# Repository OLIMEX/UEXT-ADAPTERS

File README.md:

# UEXT-ADAPTERS
Different UEXT adapters and their CAD files

Proudct pages:

[UEXT-PQ](https://www.olimex.com/Products/Modules/Adapters/UEXT-PQ/open-source-hardware), [UEXT-MPQ](https://www.olimex.com/Products/Modules/Adapters/UEXT-MPQ/open-source-hardware), [UEXT-P4Q](https://www.olimex.com/Products/Modules/Adapters/UEXT-P4Q/open-source-hardware), [RPI-UEXT-MPQ](https://www.olimex.com/Products/Modules/Adapters/RPI-UEXT-MPQ/open-source-hardware).

###Cables:

- regular size UEXT (0.1" ~ 2.54mm pitch):

https://www.olimex.com/Products/Modules/Adapters/CABLE-IDC10-15cm/

- mUEXT (0.05" ~ 1.27mm pitch): 

https://www.olimex.com/Products/Modules/Adapters/mUEXT-CABLE-10-10-1.27/

- pUEXT (1mm pitch):

https://www.olimex.com/Products/Modules/Adapters/pUEXT-CABLE-10-10-50MM/

- Qwiic (Qwiic Stemma compatible 1.0 mm):

https://www.olimex.com/Products/Modules/Adapters/QW-ST-CABLE-4-4-50MM/

###UEXT splitter:

- UEXTx5 (0.1" ~ 2.54mm step):

https://www.olimex.com/Products/Modules/Adapters/UEXTx5/open-source-hardware

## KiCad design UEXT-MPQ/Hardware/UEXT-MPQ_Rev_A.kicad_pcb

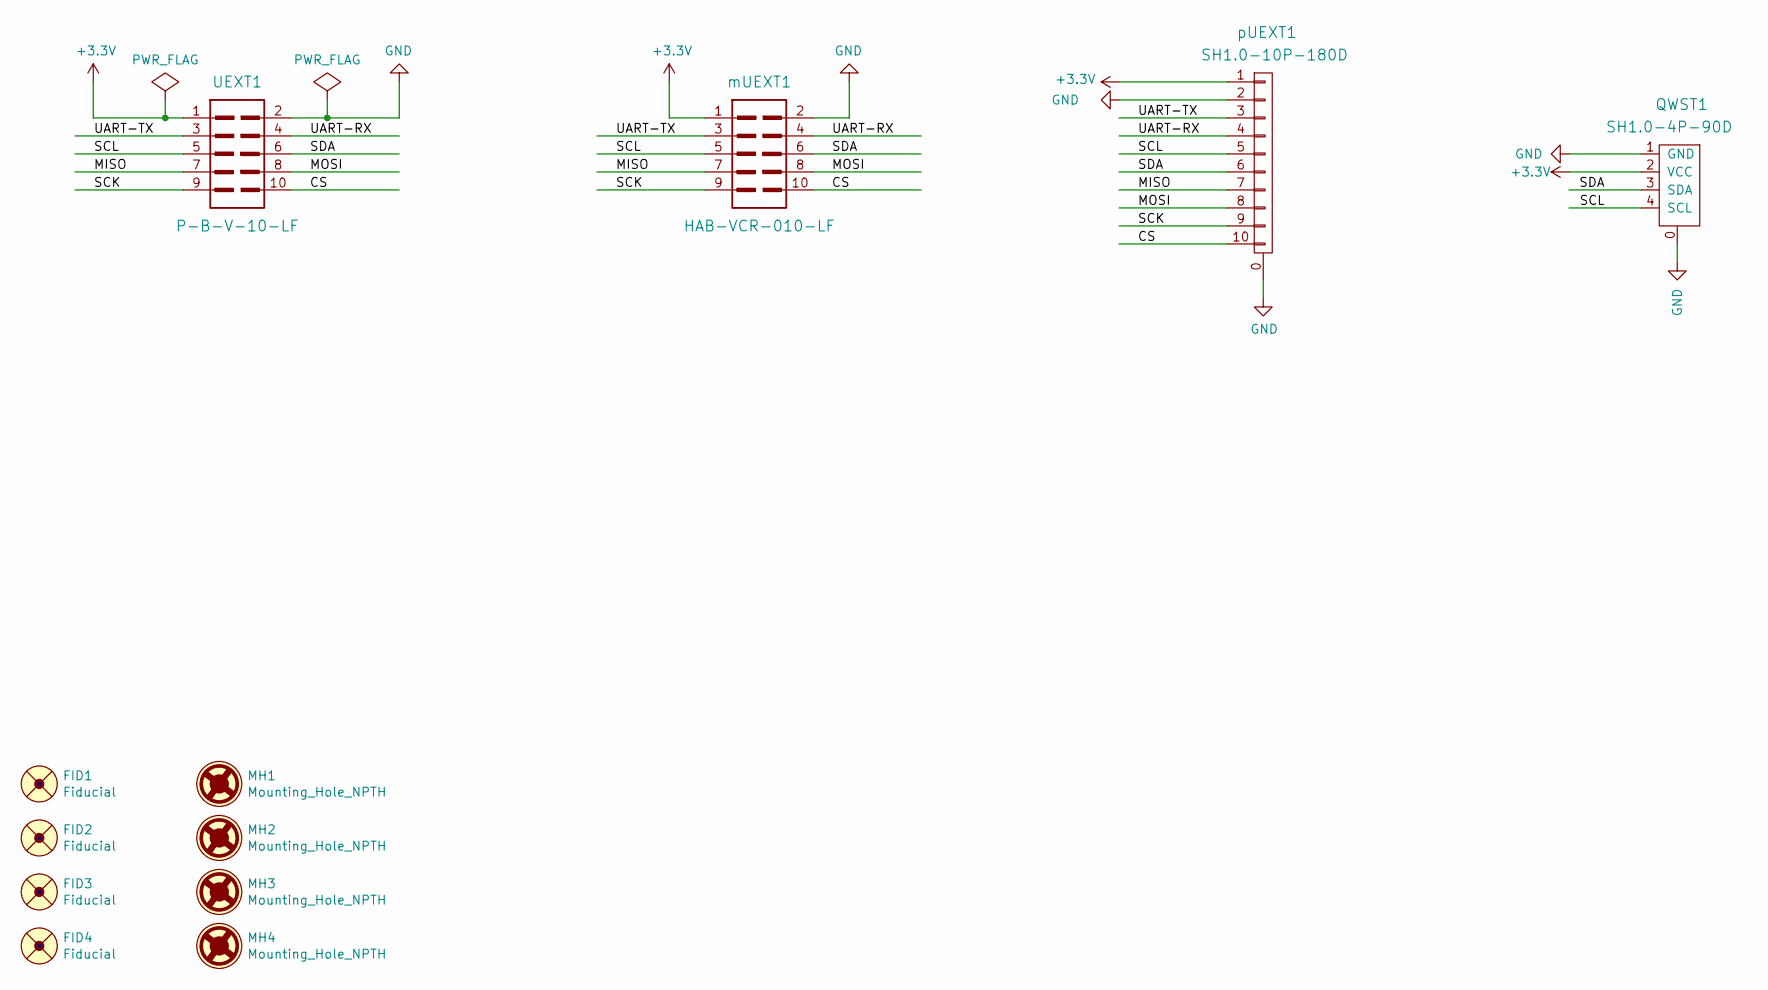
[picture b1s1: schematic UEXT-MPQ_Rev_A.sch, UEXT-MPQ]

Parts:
FID1, FID2, FID3, FID4: Fiducial; Fiducial1x3
MH1, MH2, MH3, MH4: Mounting_Hole_NPTH; Mounting_hole_3.3mm
QWST1: SH1.0-4P-90D; SM04B-SRSS-TB
UEXT1: P-B-V-10-LF; GBH-254-SMT-10
mUEXT1: HAB-VCR-010-LF
pUEXT1: SH1.0-10P-180D; BM10B-SRSS-TB

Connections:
+3.3V: QWST1.2 (VCC), UEXT1.1, mUEXT1.1, pUEXT1.1
/CS: UEXT1.10, mUEXT1.10, pUEXT1.10
/MISO: UEXT1.7, mUEXT1.7, pUEXT1.7
/MOSI: UEXT1.8, mUEXT1.8, pUEXT1.8
/SCK: UEXT1.9, mUEXT1.9, pUEXT1.9
/SCL: QWST1.4 (SCL), UEXT1.5, mUEXT1.5, pUEXT1.5
/SDA: QWST1.3 (SDA), UEXT1.6, mUEXT1.6, pUEXT1.6
/UART-RX: UEXT1.4, mUEXT1.4, pUEXT1.4
/UART-TX: UEXT1.3, mUEXT1.3, pUEXT1.3
GND: QWST1.0, QWST1.1 (GND), UEXT1.2, mUEXT1.2, pUEXT1.0, pUEXT1.2

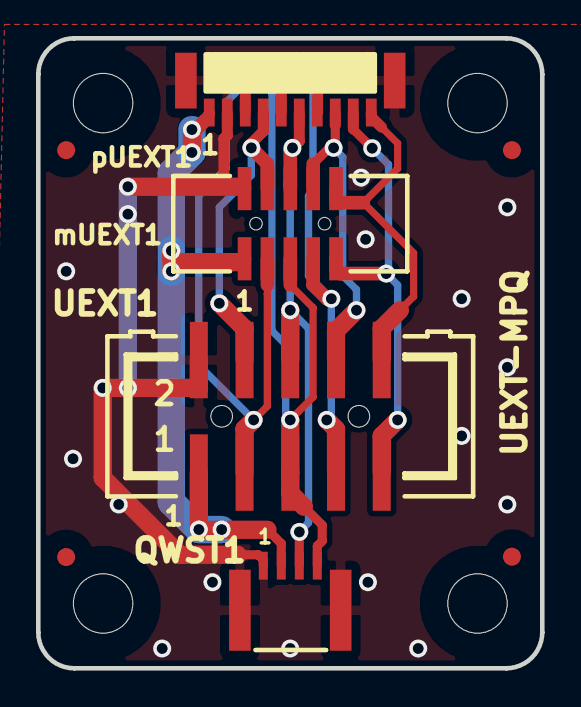
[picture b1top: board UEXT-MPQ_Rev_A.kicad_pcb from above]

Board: 2 copper layers, 28.0 x 35.0 mm, 17 parts (5 on the bottom side), 10 nets.

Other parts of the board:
Antistatic: Val**; LOGO_ANTISTATIC_1
Pb_free: LOGO_PBFREE
Recycle_bin: LOGO_RECYCLEBIN_1
Sign_CE: CE_Sign
Sign_RoHS_1: Sign_RoHS_1

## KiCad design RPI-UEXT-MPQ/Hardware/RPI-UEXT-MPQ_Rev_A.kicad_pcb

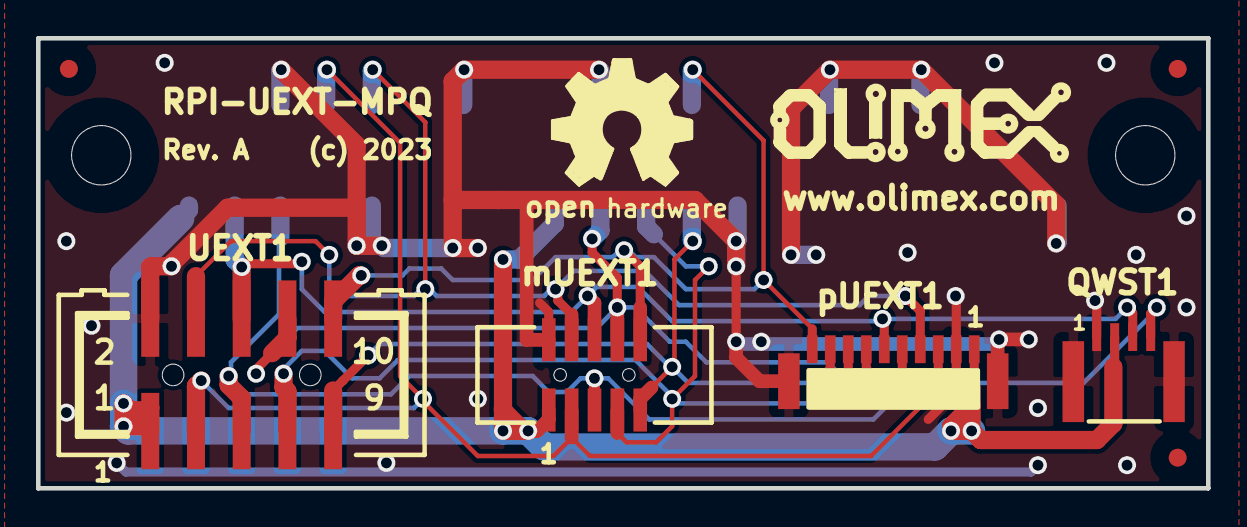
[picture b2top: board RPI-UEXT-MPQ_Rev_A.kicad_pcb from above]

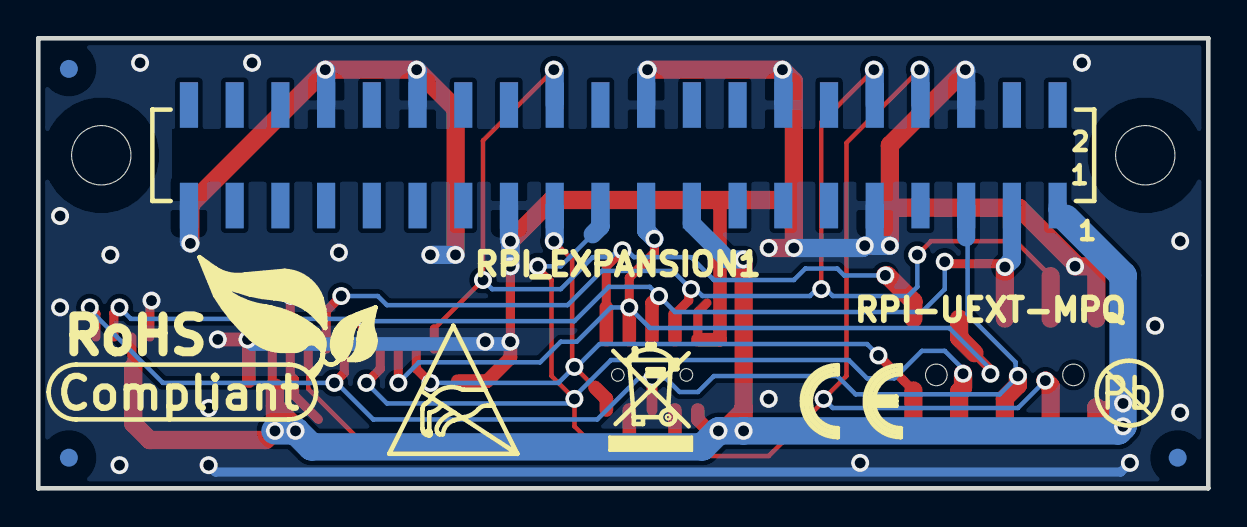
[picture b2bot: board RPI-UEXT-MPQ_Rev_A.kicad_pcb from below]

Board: 2 copper layers, 65.0 x 25.0 mm, 20 parts (9 on the bottom side), 10 nets.

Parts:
FID1, FID2, FID3, FID4, FID5, FID6: Fiducial; Fiducial1x3
Logo_OLIMEX_TB: Logo_OLIMEX_TB
MH1, MH2: Mounting_Hole_NPTH; Mounting_hole_3.3mm
QWST1: SH1.0-4P-90D; SM04B-SRSS-TB
RPI_EXPANSION1: F-V50X-2X20-LF
Sign_Antistatic: Sign_Antistatic
Sign_CE: CE_Sign
Sign_OSHW_8x8: Sign_OSHW_8x8
Sign_PB-Free: Sign_PB-Free
Sign_RecycleBin_1: Sign_RecycleBin_1
Sign_RoHS_1: Sign_RoHS_1
UEXT1: P-B-V-10-LF; GBH-254-SMT-10
mUEXT1: HAB-VCR-010-LF
pUEXT1: SH1.0-10P-180D; BM10B-SRSS-TB

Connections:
+3.3V: QWST1.2, RPI_EXPANSION1.1, RPI_EXPANSION1.17, UEXT1.1, mUEXT1.1, pUEXT1.1
/CS: RPI_EXPANSION1.24, UEXT1.10, mUEXT1.10, pUEXT1.10
/MISO: RPI_EXPANSION1.21, UEXT1.7, mUEXT1.7, pUEXT1.7
/MOSI: RPI_EXPANSION1.19, UEXT1.8, mUEXT1.8, pUEXT1.8
/SCK: RPI_EXPANSION1.23, UEXT1.9, mUEXT1.9, pUEXT1.9
/SCL: QWST1.4, RPI_EXPANSION1.5, UEXT1.5, mUEXT1.5, pUEXT1.5
/SDA: QWST1.3, RPI_EXPANSION1.3, UEXT1.6, mUEXT1.6, pUEXT1.6
/UART-RX: RPI_EXPANSION1.10, UEXT1.4, mUEXT1.4, pUEXT1.4
/UART-TX: RPI_EXPANSION1.8, UEXT1.3, mUEXT1.3, pUEXT1.3
GND: QWST1.0, QWST1.1, RPI_EXPANSION1.6, RPI_EXPANSION1.9, RPI_EXPANSION1.14, RPI_EXPANSION1.20, RPI_EXPANSION1.25, RPI_EXPANSION1.30, RPI_EXPANSION1.34, RPI_EXPANSION1.39, UEXT1.2, mUEXT1.2, pUEXT1.0, pUEXT1.2

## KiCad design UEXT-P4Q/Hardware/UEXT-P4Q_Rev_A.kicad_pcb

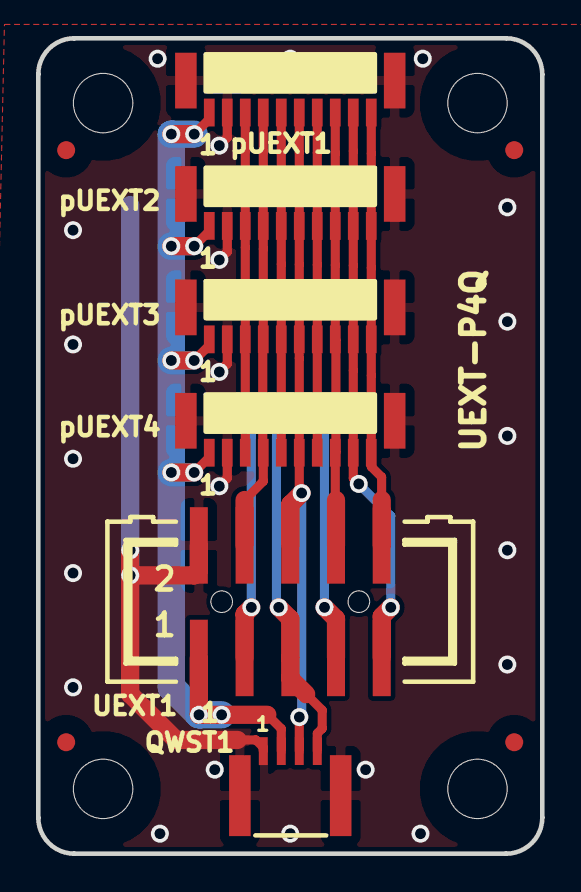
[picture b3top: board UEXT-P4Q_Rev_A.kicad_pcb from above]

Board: 2 copper layers, 28.0 x 45.3 mm, 19 parts (5 on the bottom side), 10 nets.

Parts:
Antistatic: Val**; LOGO_ANTISTATIC_1
FID1, FID2, FID3, FID4: Fiducial; Fiducial1x3
MH1, MH2, MH3, MH4: Mounting_Hole_NPTH; Mounting_hole_3.3mm
Pb_free: LOGO_PBFREE
QWST1: SH1.0-4P-90D; SM04B-SRSS-TB
Recycle_bin: LOGO_RECYCLEBIN_1
Sign_CE: CE_Sign
Sign_RoHS_1: Sign_RoHS_1
UEXT1: P-B-V-10-LF; GBH-254-SMT-10
pUEXT1, pUEXT2, pUEXT3, pUEXT4: SH1.0-10P-180D; BM10B-SRSS-TB

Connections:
+3.3V: QWST1.2, UEXT1.1, pUEXT1.1, pUEXT2.1, pUEXT3.1, pUEXT4.1
/CS: UEXT1.10, pUEXT1.10, pUEXT2.10, pUEXT3.10, pUEXT4.10
/MISO: UEXT1.7, pUEXT1.7, pUEXT2.7, pUEXT3.7, pUEXT4.7
/MOSI: UEXT1.8, pUEXT1.8, pUEXT2.8, pUEXT3.8, pUEXT4.8
/SCK: UEXT1.9, pUEXT1.9, pUEXT2.9, pUEXT3.9, pUEXT4.9
/SCL: QWST1.4, UEXT1.5, pUEXT1.5, pUEXT2.5, pUEXT3.5, pUEXT4.5
/SDA: QWST1.3, UEXT1.6, pUEXT1.6, pUEXT2.6, pUEXT3.6, pUEXT4.6
/UART-RX: UEXT1.4, pUEXT1.4, pUEXT2.4, pUEXT3.4, pUEXT4.4
/UART-TX: UEXT1.3, pUEXT1.3, pUEXT2.3, pUEXT3.3, pUEXT4.3
GND: QWST1.0, QWST1.1, UEXT1.2, pUEXT1.0, pUEXT1.2, pUEXT2.0, pUEXT2.2, pUEXT3.0, pUEXT3.2, pUEXT4.0, pUEXT4.2

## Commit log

2023-10-27 Update
    Added hardware sources

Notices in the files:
RPI-UEXT-MPQ/Hardware/RPI-UEXT-MPQ_Rev_A.kicad_pcb:
(c) 2023
UEXT-MPQ/Hardware/UEXT-MPQ_Rev_A.kicad_pcb:
(c) 2021
